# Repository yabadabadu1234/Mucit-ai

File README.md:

# Mucit-ai

## Kur'an Hikmetleri

Kur'an-ı Kerîm'in sûre, nüzûl, tertip ve ayet haritalarını; grafik, sûre dosyaları ve derlenmiş kitabı içeren çalışma.

- **Okunabilir kitap (GitHub Pages):**

- https://yabadabadu1234.github.io/Mucit-ai/
- PDF: [`kuran_hikmetleri/kuran_hikmetleri.pdf`](kuran_hikmetleri/kuran_hikmetleri.pdf)
- Fihrist: [`kuran_hikmetleri/00_FIHRIST.md`](kuran_hikmetleri/00_FIHRIST.md)

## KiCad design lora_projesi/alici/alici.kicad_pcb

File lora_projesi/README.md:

# LoRa remote + receiver – hardware design

- verici/ : transmitter – KiCad files, uretim_dosyalari/ (Gerber, drill, BOM, placement, PDFs), TASARIM_NOTU.md
- alici/ : receiver – KiCad files, uretim_dosyalari/ (Gerber, drill, BOM, placement, PDFs), TASARIM_NOTU.md
- simulasyon/ : ngspice netlists (relay driver, 12 V input protection)
- uretim/ : Python generators (schematic, PCB placement, routing with Freerouting, outputs)
- teklif_taslagi.md, teklif_kisa.txt : offer texts

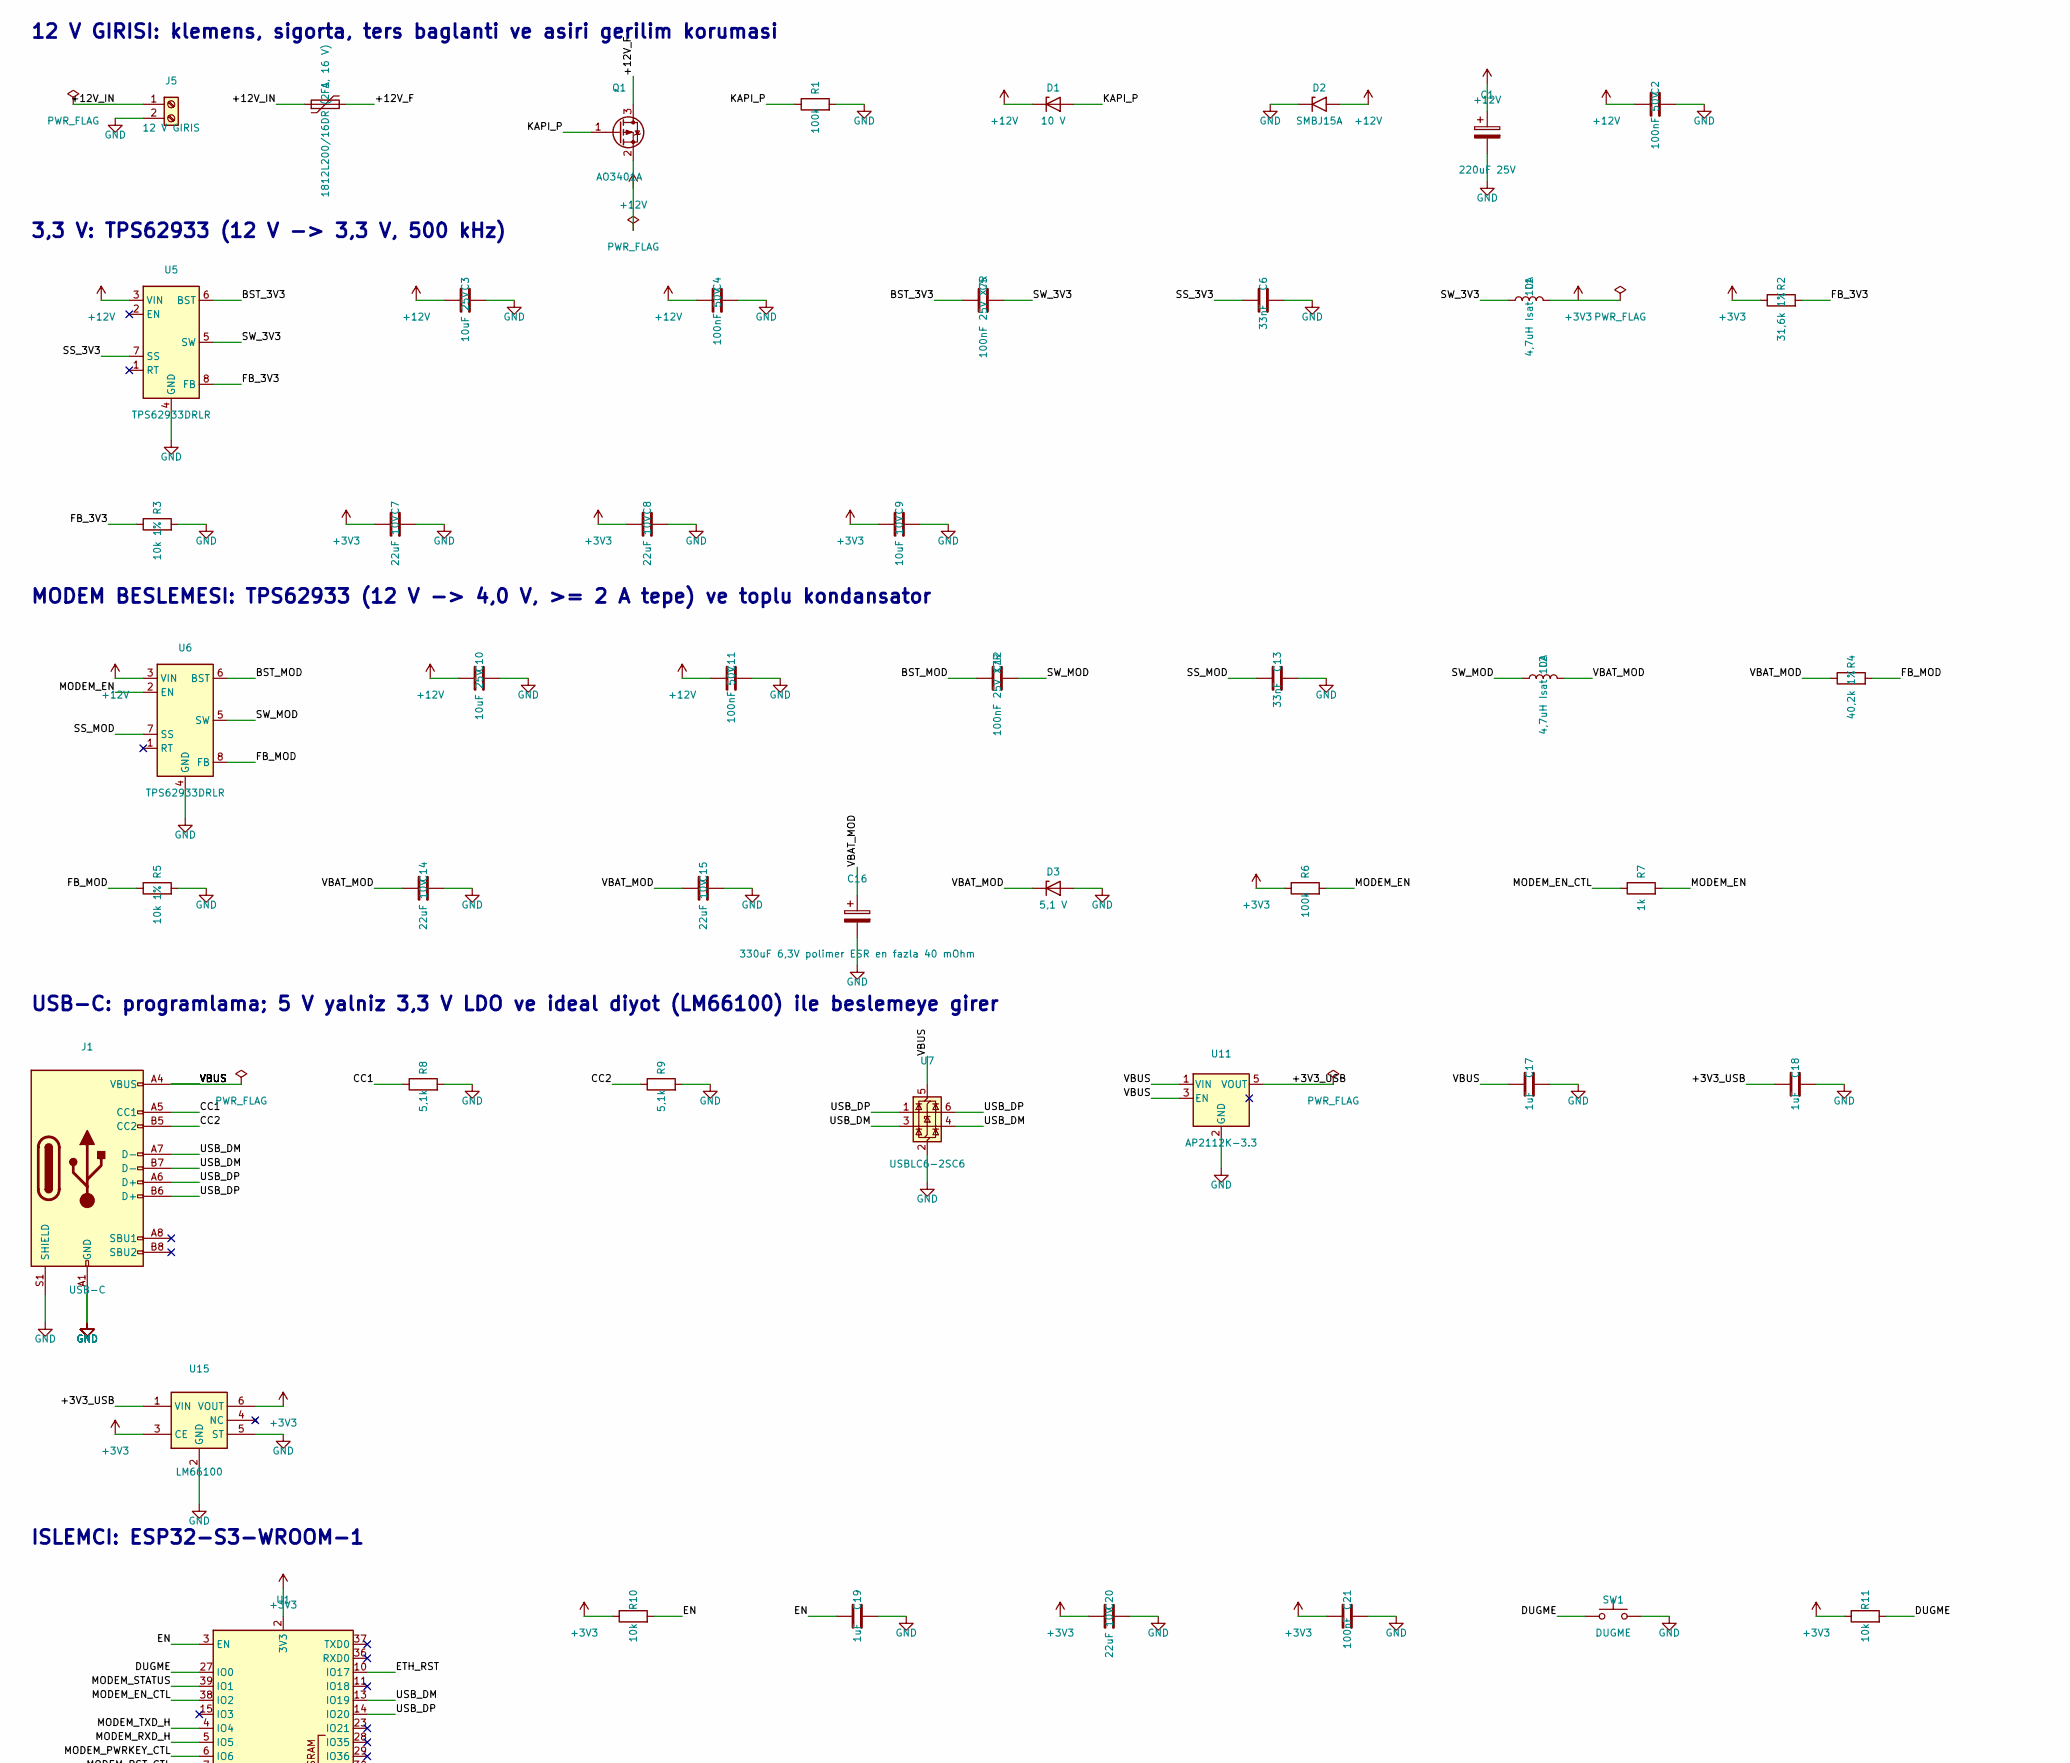
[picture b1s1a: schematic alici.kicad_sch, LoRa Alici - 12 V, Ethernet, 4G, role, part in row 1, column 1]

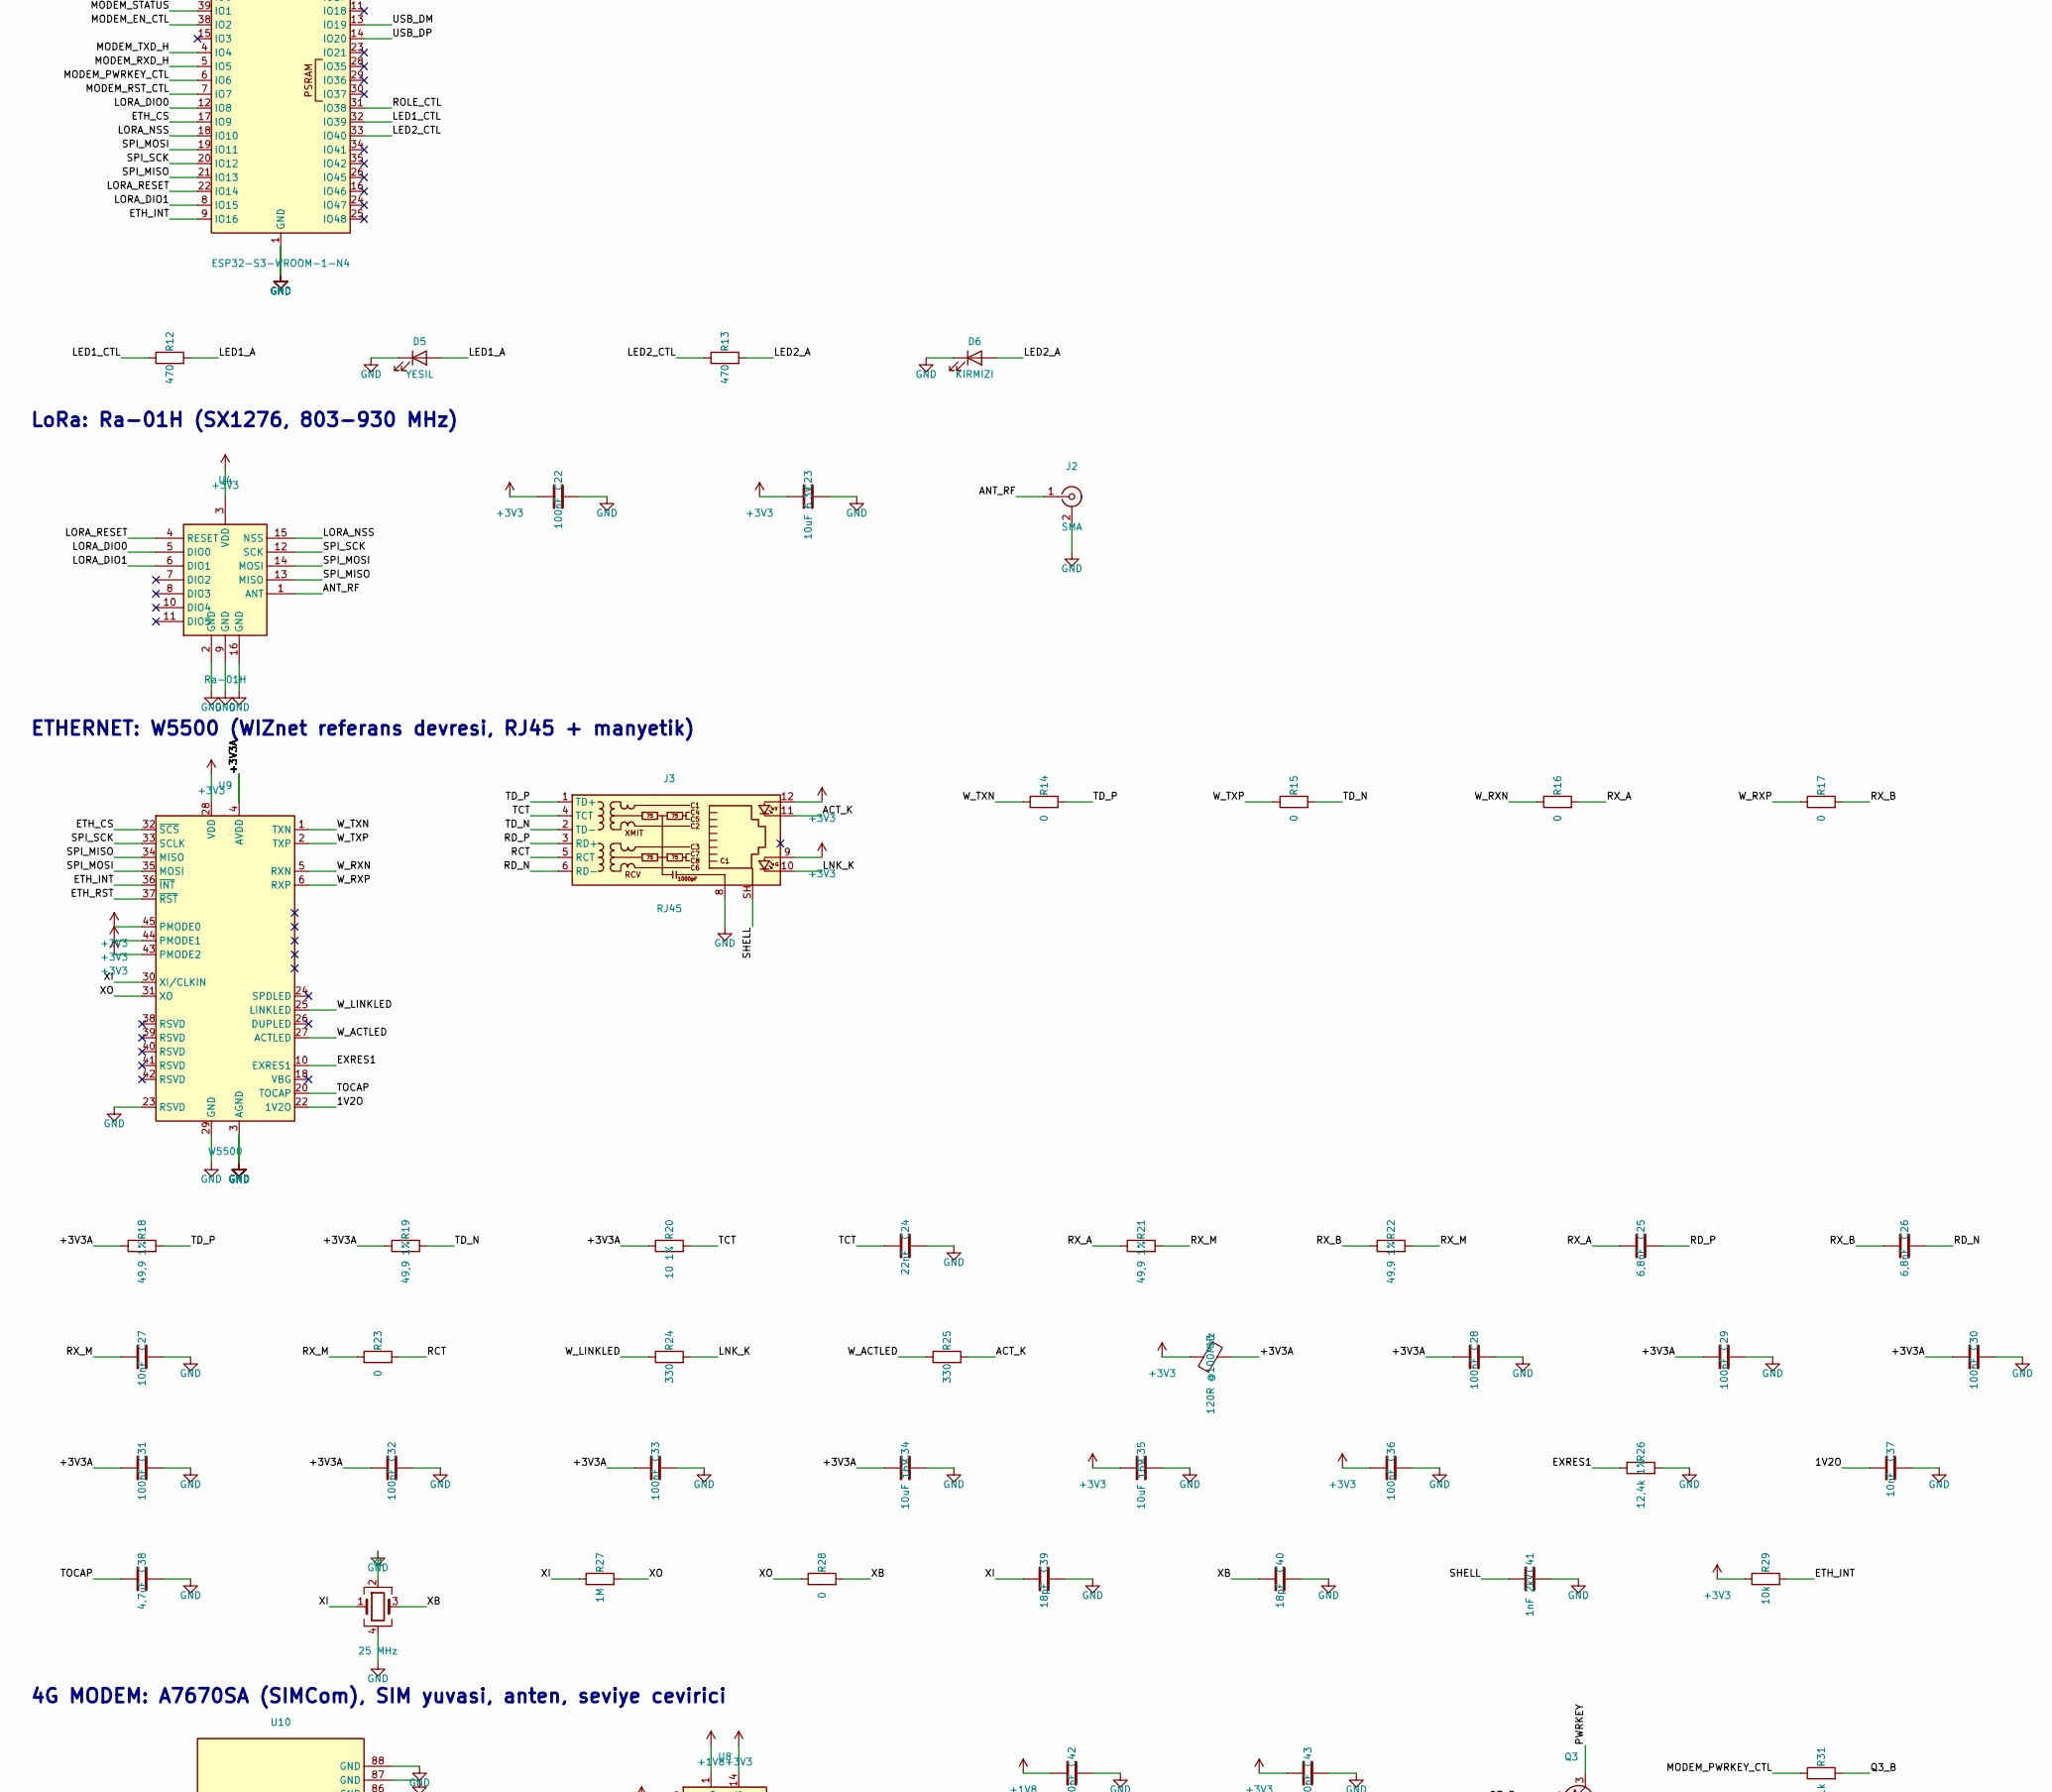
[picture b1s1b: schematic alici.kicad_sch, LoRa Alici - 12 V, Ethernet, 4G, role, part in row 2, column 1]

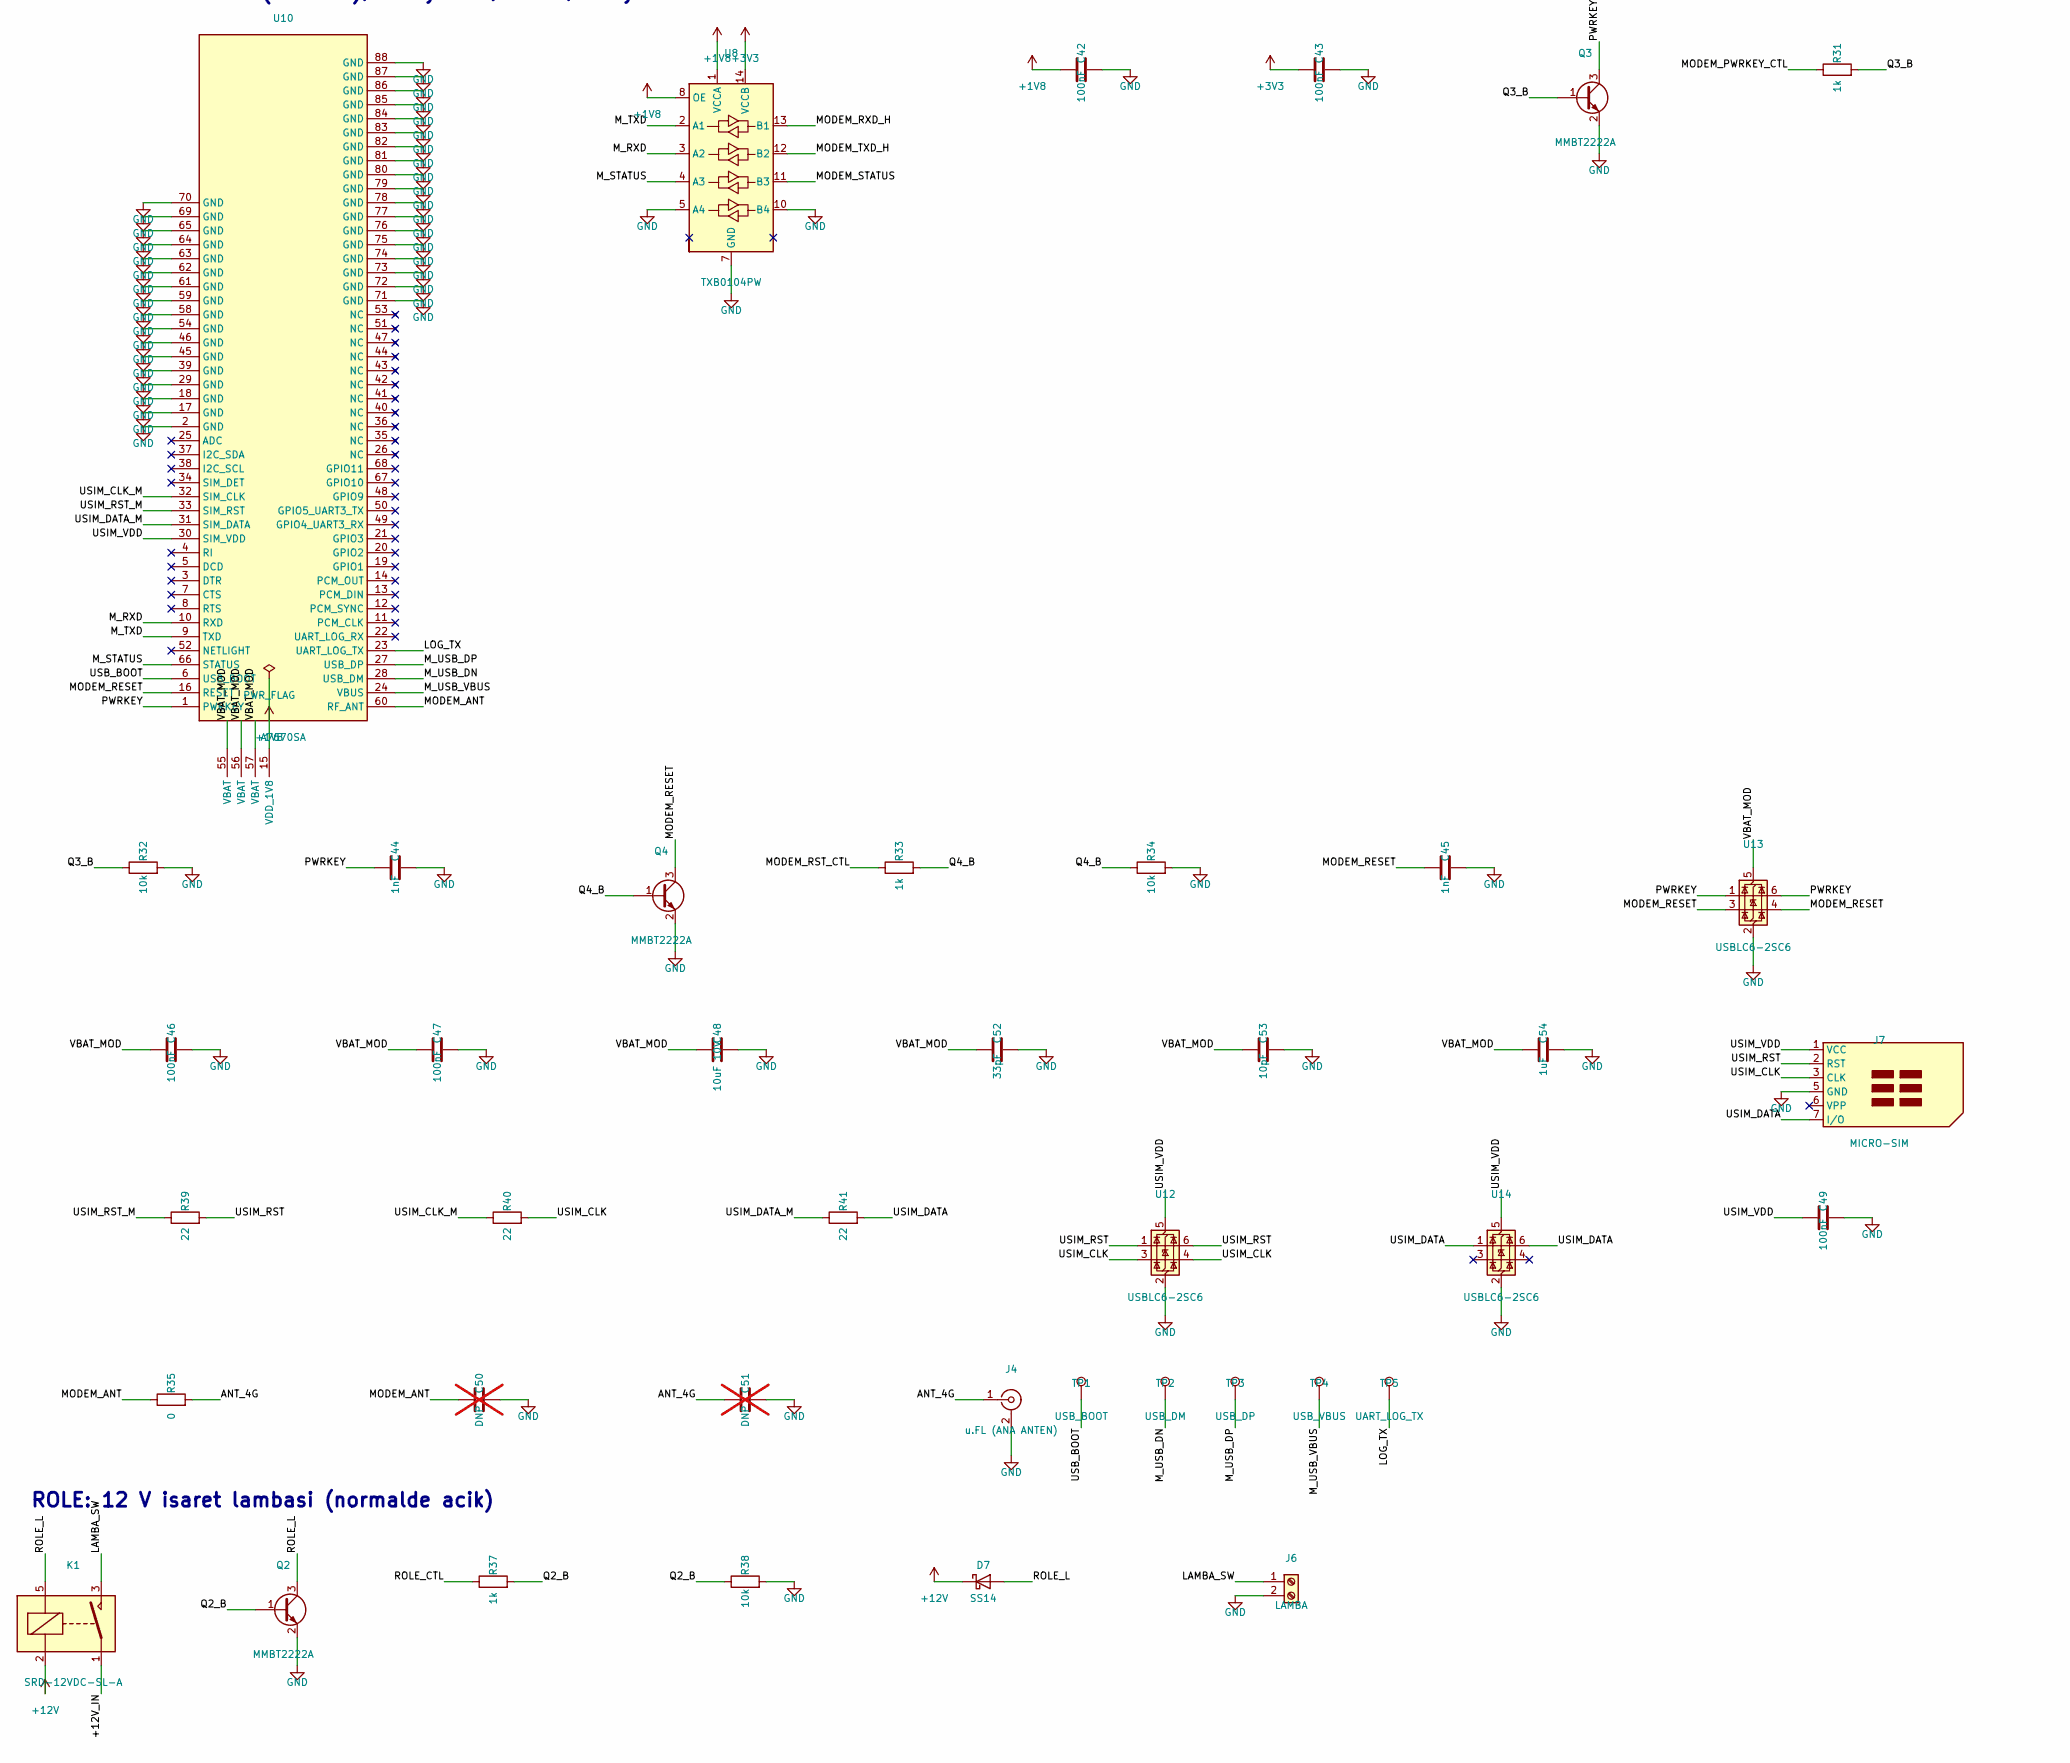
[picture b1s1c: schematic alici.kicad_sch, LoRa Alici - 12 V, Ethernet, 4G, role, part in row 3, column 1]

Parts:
C1: 220uF 25V; CP_Elec_8x10
C2, C4, C11: 100nF 50V; C_0603_1608Metric
C3, C10: 10uF 25V; C_1206_3216Metric
C5, C12: 100nF 25V X7R; C_0603_1608Metric
C6, C13: 33nF; C_0603_1608Metric
C7, C8, C14, C15: 22uF 10V; C_1206_3216Metric
C9, C48: 10uF 10V; C_0603_1608Metric
C16: 330uF 6,3V polimer ESR en fazla 40 mOhm; CP_Elec_6.3x7.7
C17, C18, C19, C54: 1uF; C_0603_1608Metric
C20: 22uF 10V; C_0805_2012Metric
C21, C22, C28, C29, C30, C31, C32, C33, C36, C42, C43, C46, C47, C49: 100nF; C_0603_1608Metric
C23: 10uF 6,3V; C_0603_1608Metric
C24: 22nF; C_0603_1608Metric
C25, C26: 6,8nF; C_0603_1608Metric
C27, C37: 10nF; C_0603_1608Metric
C34, C35: 10uF 16V; C_0603_1608Metric
C38: 4,7uF; C_0603_1608Metric
C39, C40: 18pF; C_0603_1608Metric
C41: 1nF 2kV; C_1206_3216Metric
C44, C45: 1nF; C_0603_1608Metric; MPN A7670 belgesi: PWRKEY ve RESET uzerinde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
C50, C51: DNP; C_0603_1608Metric; not fitted
C52: 33pF; C_0603_1608Metric
C53: 10pF; C_0603_1608Metric
D1: 10 V; D_SOD-123; MPN BZT52C10 (10 V zener)
D2: SMBJ15A; D_SMB; MPN SMBJ15A (tek yonlu 15 V TVS)
D3: 5,1 V; D_SOD-123; MPN BZT52C5V1 (SIMCom onerisi, 500 mW)
D5: YESIL; LED_0603_1608Metric
D6: KIRMIZI; LED_0603_1608Metric
D7: SS14; D_SMA; MPN SS14
F1: 1812L200/16DR (2 A, 16 V); Fuse_1812_4532Metric; MPN Littelfuse 1812L200/16DR (tutma 2 A, 16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
J1: USB-C; USB_C_Receptacle_GCT_USB4105-xx-A_16P_TopMnt_Horizontal; MPN GCT USB4105-GF-A
J2: SMA; SMA_Amphenol_132289_EdgeMount; MPN Amphenol 132289 (kenar SMA)
J3: RJ45; RJ45_Hanrun_HR911105A_Horizontal; MPN HanRun HR911105A
J4: u.FL (ANA ANTEN); U.FL_Hirose_U.FL-R-SMT-1_Vertical; MPN Hirose U.FL-R-SMT-1(10)
J5: 12 V GIRIS; TerminalBlock_Phoenix_MKDS-1,5-2-5.08_1x02_P5.08mm_Horizont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
J6: LAMBA; TerminalBlock_Phoenix_MKDS-1,5-2-5.08_1x02_P5.08mm_Horizont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
J7: MICRO-SIM; microSIM_JAE_SF53S006VCBR2000; MPN JAE SF53S006VCBR2000 (6 uclu micro-SIM)
K1: SRD-12VDC-SL-A; Relay_SPST_SANYOU_SRD_Series_Form_A; MPN Songle SRD-12VDC-SL-A (bobin 400 ohm, k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
L1, L2: 4,7uH Isat 10A; L_Bourns_SRP7028A_7.3x6.6mm; MPN Bourns SRP7028A-4R7M (Isat 10 A, Irms 5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
L3: 120R @100MHz; L_0603_1608Metric; MPN HH-1M1608-121JT (WIZnet referansi)
Q1: AO3401A; SOT-23; MPN AO3401A
Q2, Q3, Q4: MMBT2222A; SOT-23; MPN MMBT2222A
R1, R6: 100k; R_0603_1608Metric
R2: 31,6k 1%; R_0603_1608Metric
R3, R5: 10k 1%; R_0603_1608Metric
R4: 40,2k 1%; R_0603_1608Metric
R7, R31, R33, R37: 1k; R_0603_1608Metric
R8, R9: 5,1k; R_0603_1608Metric
R10, R11, R29, R32, R34, R38: 10k; R_0603_1608Metric
R12, R13: 470; R_0603_1608Metric
R14, R15, R16, R17, R23, R28, R35: 0; R_0603_1608Metric
R18, R19, R21, R22: 49,9 1%; R_0603_1608Metric
R20: 10 1%; R_0603_1608Metric
R24, R25: 330; R_0603_1608Metric
R26: 12,4k 1%; R_0603_1608Metric
R27: 1M; R_0603_1608Metric
R39, R40, R41: 22; R_0603_1608Metric; MPN A7670 belgesi Sekil 19: SIM hatlarina 2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
SW1: DUGME; SW_SPST_TL3342
TP1: USB_BOOT; TestPoint_Pad_1.0x1.0mm
TP2: USB_DM; TestPoint_Pad_1.0x1.0mm
TP3: USB_DP; TestPoint_Pad_1.0x1.0mm
TP4: USB_VBUS; TestPoint_Pad_1.0x1.0mm
TP5: UART_LOG_TX; TestPoint_Pad_1.0x1.0mm
U1: ESP32-S3-WROOM-1-N4; ESP32-S3-WROOM-1; MPN ESP32-S3-WROOM-1-N4
U4: Ra-01H; MPN Ai-Thinker Ra-01H (LCSC C503593)
U5, U6: TPS62933DRLR; SOT-583-8; MPN TPS62933DRLR
U7: USBLC6-2SC6; SOT-23-6; MPN USBLC6-2SC6
U8: TXB0104PW; TSSOP-14_4.4x5mm_P0.65mm; MPN TXB0104PWR
U9: W5500; LQFP-48_7x7mm_P0.5mm; MPN W5500
U10: A7670SA; A7670SA_LGA88; MPN SIMCom A7670SA-LASE (LCSC C47088708; LT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
U11: AP2112K-3.3; SOT-23-5; MPN AP2112K-3.3TRG1
U12: USBLC6-2SC6; SOT-23-6; MPN USBLC6-2SC6 (SIM RST ve CLK ESD; SIMCom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
U13: USBLC6-2SC6; SOT-23-6; MPN USBLC6-2SC6 (PWRKEY ve RESET ESD, hat b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
U14: USBLC6-2SC6; SOT-23-6; MPN USBLC6-2SC6 (SIM DATA ESD; ikinci hat k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
U15: LM66100; SOT-363_SC-70-6; MPN TI LM66100DCKR (ideal diyot, 79-91 mOhm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
Y1: 25 MHz; Crystal_SMD_3225-4Pin_3.2x2.5mm; MPN 25 MHz, 18 pF yuk, +-30 ppm, C0 en fazl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

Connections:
1V2O: C37.1, U9.22 (1V2O)
+1V8: C42.1, U8.1 (VCCA), U8.8 (OE), U10.15 (VDD_1V8)
+3V3: C7.1, C8.1, C9.1, C20.1, C21.1, C22.1, C23.1, C35.1, C36.1, C43.1, J3.9, J3.12, L1.2, L3.1, R2.1, R6.1, R10.1, R11.1, R29.1, U1.2 (3V3), U4.3 (VDD), U8.14 (VCCB), U9.28 (VDD), U9.43 (PMODE2), U9.44 (PMODE1), U9.45 (PMODE0), U15.3 (CE), U15.6 (VOUT)
+3V3A: C28.1, C29.1, C30.1, C31.1, C32.1, C33.1, C34.1, L3.2, R18.1, R19.1, R20.1, U9.4 (AVDD), U9.8 (AVDD), U9.11 (AVDD), U9.15 (AVDD), U9.17 (AVDD), U9.21 (AVDD)
+3V3_USB: C18.1, U11.5 (VOUT), U15.1 (VIN)
+12V: C1.1, C2.1, C3.1, C4.1, C10.1, C11.1, D1.1 (K), D2.2 (A2), D7.1 (K), K1.2, Q1.2 (S), U5.3 (VIN), U6.3 (VIN)
+12V_F: F1.2, Q1.3 (D)
+12V_IN: F1.1, J5.1, K1.1
ACT_K: J3.11, R25.2
ANT_4G: C51.1, J4.1 (In), R35.2
ANT_RF: J2.1 (In), U4.1 (ANT)
BST_3V3: C5.1, U5.6 (BST)
BST_MOD: C12.1, U6.6 (BST)
CC1: J1.A5 (CC1), R8.1
CC2: J1.B5 (CC2), R9.1
DUGME: R11.2, SW1.1, U1.27 (IO0)
EN: C19.1, R10.2, U1.3 (EN)
ETH_CS: U1.17 (IO9), U9.32 (~SCS)
ETH_INT: R29.2, U1.9 (IO16), U9.36 (~INT)
ETH_RST: U1.10 (IO17), U9.37 (~RST)
EXRES1: R26.1, U9.10 (EXRES1)
FB_3V3: R2.2, R3.1, U5.8 (FB)
FB_MOD: R4.2, R5.1, U6.8 (FB)
GND: C1.2, C2.2, C3.2, C4.2, C6.2, C7.2, C8.2, C9.2, C10.2, C11.2, C13.2, C14.2, C15.2, C16.2, C17.2, C18.2, C19.2, C20.2, C21.2, C22.2, C23.2, C24.2, C27.2, C28.2, C29.2, C30.2, C31.2, C32.2, C33.2, C34.2, C35.2, C36.2, C37.2, C38.2, C39.2, C40.2, C41.2, C42.2, C43.2, C44.2, C45.2, C46.2, C47.2, C48.2, C49.2, C50.2, C51.2, C52.2, C53.2, C54.2, D2.1 (A1), D3.2 (A), D5.1 (K), D6.1 (K), J1.A1 (GND), J1.A12 (GND), J1.B1 (GND), J1.B12 (GND), J1.S1 (SHIELD), J2.2 (Ext), J3.8, J4.2 (Ext), J5.2, J6.2, J7.5 (GND), Q2.2 (E), Q3.2 (E), Q4.2 (E), R1.2, R3.2, R5.2, R8.2, R9.2, R26.2, R32.2, R34.2, R38.2, SW1.2, U1.1 (GND), U1.40 (GND), U1.41 (GND), U4.2 (GND), U4.9 (GND), U4.16 (GND), U5.4 (GND), U6.4 (GND), U7.2 (GND), U8.5 (A4), U8.7 (GND), U8.10 (B4), U9.3 (AGND), U9.9 (AGND), U9.14 (AGND), U9.16 (AGND), U9.19 (AGND), U9.23 (RSVD), U9.29 (GND), U9.48 (AGND), U10.2 (GND), U10.17 (GND), U10.18 (GND), U10.29 (GND), U10.39 (GND), U10.45 (GND), U10.46 (GND), U10.54 (GND), U10.58 (GND), U10.59 (GND), U10.61 (GND), U10.62 (GND), U10.63 (GND), U10.64 (GND), U10.65 (GND), U10.69 (GND), U10.70 (GND), U10.71 (GND), U10.72 (GND), U10.73 (GND), U10.74 (GND), U10.75 (GND), U10.76 (GND), U10.77 (GND), U10.78 (GND), U10.79 (GND), U10.80 (GND), U10.81 (GND), U10.82 (GND), U10.83 (GND), U10.84 (GND), U10.85 (GND), U10.86 (GND), U10.87 (GND), U10.88 (GND), U11.2 (GND), U12.2 (GND), U13.2 (GND), U14.2 (GND), U15.2 (GND), U15.5 (ST), Y1.2, Y1.4
KAPI_P: D1.2 (A), Q1.1 (G), R1.1
LAMBA_SW: J6.1, K1.3
LED1_A: D5.2 (A), R12.2
LED1_CTL: R12.1, U1.32 (IO39)
LED2_A: D6.2 (A), R13.2
LED2_CTL: R13.1, U1.33 (IO40)
LNK_K: J3.10, R24.2
LOG_TX: TP5.1, U10.23 (UART_LOG_TX)
LORA_DIO0: U1.12 (IO8), U4.5 (DIO0)
LORA_DIO1: U1.8 (IO15), U4.6 (DIO1)
LORA_NSS: U1.18 (IO10), U4.15 (NSS)
LORA_RESET: U1.22 (IO14), U4.4 (RESET)
MODEM_ANT: C50.1, R35.1, U10.60 (RF_ANT)
MODEM_EN: R6.2, R7.2, U6.2 (EN)
MODEM_EN_CTL: R7.1, U1.38 (IO2)
MODEM_PWRKEY_CTL: R31.1, U1.6 (IO6)
MODEM_RESET: C45.1, Q4.3 (C), U10.16 (RESET), U13.3 (I/O2), U13.4 (I/O2)
MODEM_RST_CTL: R33.1, U1.7 (IO7)
MODEM_RXD_H: U1.5 (IO5), U8.13 (B1)
MODEM_STATUS: U1.39 (IO1), U8.11 (B3)
MODEM_TXD_H: U1.4 (IO4), U8.12 (B2)
M_RXD: U8.3 (A2), U10.10 (RXD)
M_STATUS: U8.4 (A3), U10.66 (STATUS)
M_TXD: U8.2 (A1), U10.9 (TXD)
M_USB_DN: TP2.1, U10.28 (USB_DM)
M_USB_DP: TP3.1, U10.27 (USB_DP)
M_USB_VBUS: TP4.1, U10.24 (VBUS)
PWRKEY: C44.1, Q3.3 (C), U10.1 (PWRKEY), U13.1 (I/O1), U13.6 (I/O1)
Q2_B: Q2.1 (B), R37.2, R38.1
Q3_B: Q3.1 (B), R31.2, R32.1
Q4_B: Q4.1 (B), R33.2, R34.1
RCT: J3.5 (RCT), R23.2
RD_N: C26.2, J3.6 (RD-)
RD_P: C25.2, J3.3 (RD+)
ROLE_CTL: R37.1, U1.31 (IO38)
ROLE_L: D7.2 (A), K1.5, Q2.3 (C)
RX_A: C25.1, R16.2, R21.1
RX_B: C26.1, R17.2, R22.1
RX_M: C27.1, R21.2, R22.2, R23.1
SHELL: C41.1, J3.SH
SPI_MISO: U1.21 (IO13), U4.13 (MISO), U9.34 (MISO)
SPI_MOSI: U1.19 (IO11), U4.14 (MOSI), U9.35 (MOSI)
SPI_SCK: U1.20 (IO12), U4.12 (SCK), U9.33 (SCLK)
SS_3V3: C6.1, U5.7 (SS)
SS_MOD: C13.1, U6.7 (SS)
SW_3V3: C5.2, L1.1, U5.5 (SW)
SW_MOD: C12.2, L2.1, U6.5 (SW)
TCT: C24.1, J3.4 (TCT), R20.2
TD_N: J3.2 (TD-), R15.2, R19.2
TD_P: J3.1 (TD+), R14.2, R18.2
TOCAP: C38.1, U9.20 (TOCAP)
USB_BOOT: TP1.1, U10.6 (USB_BOOT)
USB_DM: J1.A7 (D-), J1.B7 (D-), U1.13 (IO19), U7.3 (I/O2), U7.4 (I/O2)
USB_DP: J1.A6 (D+), J1.B6 (D+), U1.14 (IO20), U7.1 (I/O1), U7.6 (I/O1)
USIM_CLK: J7.3 (CLK), R40.2, U12.3 (I/O2), U12.4 (I/O2)
USIM_CLK_M: R40.1, U10.32 (SIM_CLK)
USIM_DATA: J7.7 (I/O), R41.2, U14.1 (I/O1), U14.6 (I/O1)
USIM_DATA_M: R41.1, U10.31 (SIM_DATA)
USIM_RST: J7.2 (RST), R39.2, U12.1 (I/O1), U12.6 (I/O1)
USIM_RST_M: R39.1, U10.33 (SIM_RST)
USIM_VDD: C49.1, J7.1 (VCC), U10.30 (SIM_VDD), U12.5 (VBUS), U14.5 (VBUS)
VBAT_MOD: C14.1, C15.1, C16.1, C46.1, C47.1, C48.1, C52.1, C53.1, C54.1, D3.1 (K), L2.2, R4.1, U10.55 (VBAT), U10.56 (VBAT), U10.57 (VBAT), U13.5 (VBUS)
VBUS: C17.1, J1.A4 (VBUS), J1.A9 (VBUS), J1.B4 (VBUS), J1.B9 (VBUS), U7.5 (VBUS), U11.1 (VIN), U11.3 (EN)
W_ACTLED: R25.1, U9.27 (ACTLED)
W_LINKLED: R24.1, U9.25 (LINKLED)
W_RXN: R16.1, U9.5 (RXN)
W_RXP: R17.1, U9.6 (RXP)
W_TXN: R14.1, U9.1 (TXN)
W_TXP: R15.1, U9.2 (TXP)
XB: C40.1, R28.2, Y1.3
XI: C39.1, R27.1, U9.30 (XI/CLKIN), Y1.1
XO: R27.2, R28.1, U9.31 (XO)

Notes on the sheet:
12 V GIRISI: klemens, sigorta, ters baglanti ve asiri gerilim korumasi
3,3 V: TPS62933 (12 V -> 3,3 V, 500 kHz)
MODEM BESLEMESI: TPS62933 (12 V -> 4,0 V, >= 2 A tepe) ve toplu kondansator
USB-C: programlama; 5 V yalniz 3,3 V LDO ve ideal diyot (LM66100) ile beslemeye girer
ISLEMCI: ESP32-S3-WROOM-1
LoRa: Ra-01H (SX1276, 803-930 MHz)
ETHERNET: W5500 (WIZnet referans devresi, RJ45 + manyetik)
4G MODEM: A7670SA (SIMCom), SIM yuvasi, anten, seviye cevirici
ROLE: 12 V isaret lambasi (normalde acik)

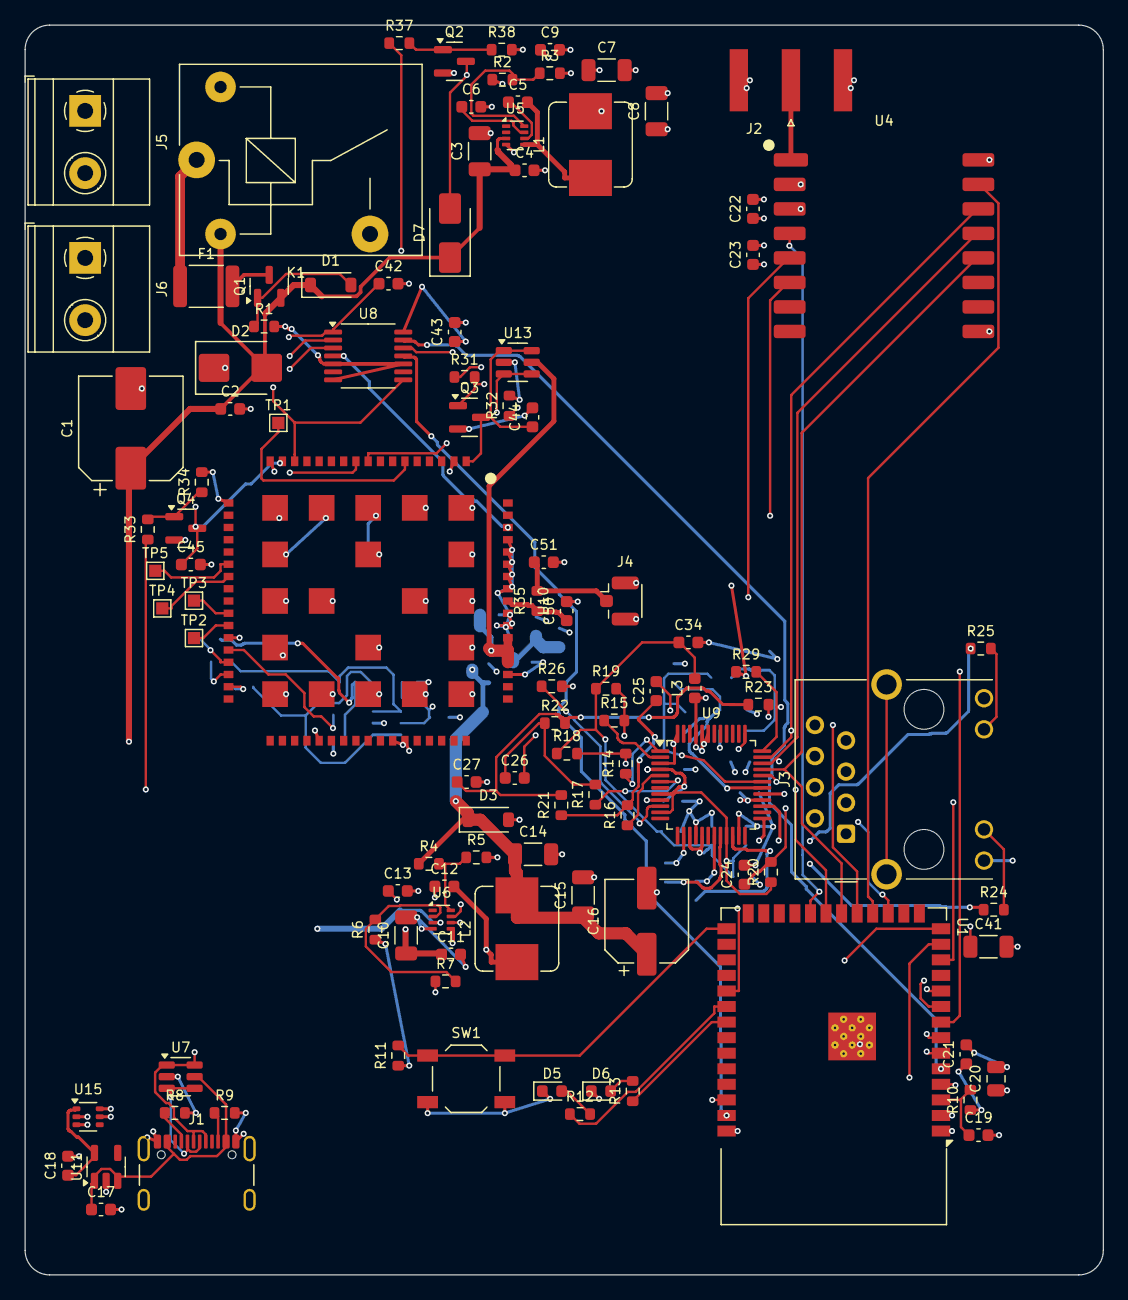
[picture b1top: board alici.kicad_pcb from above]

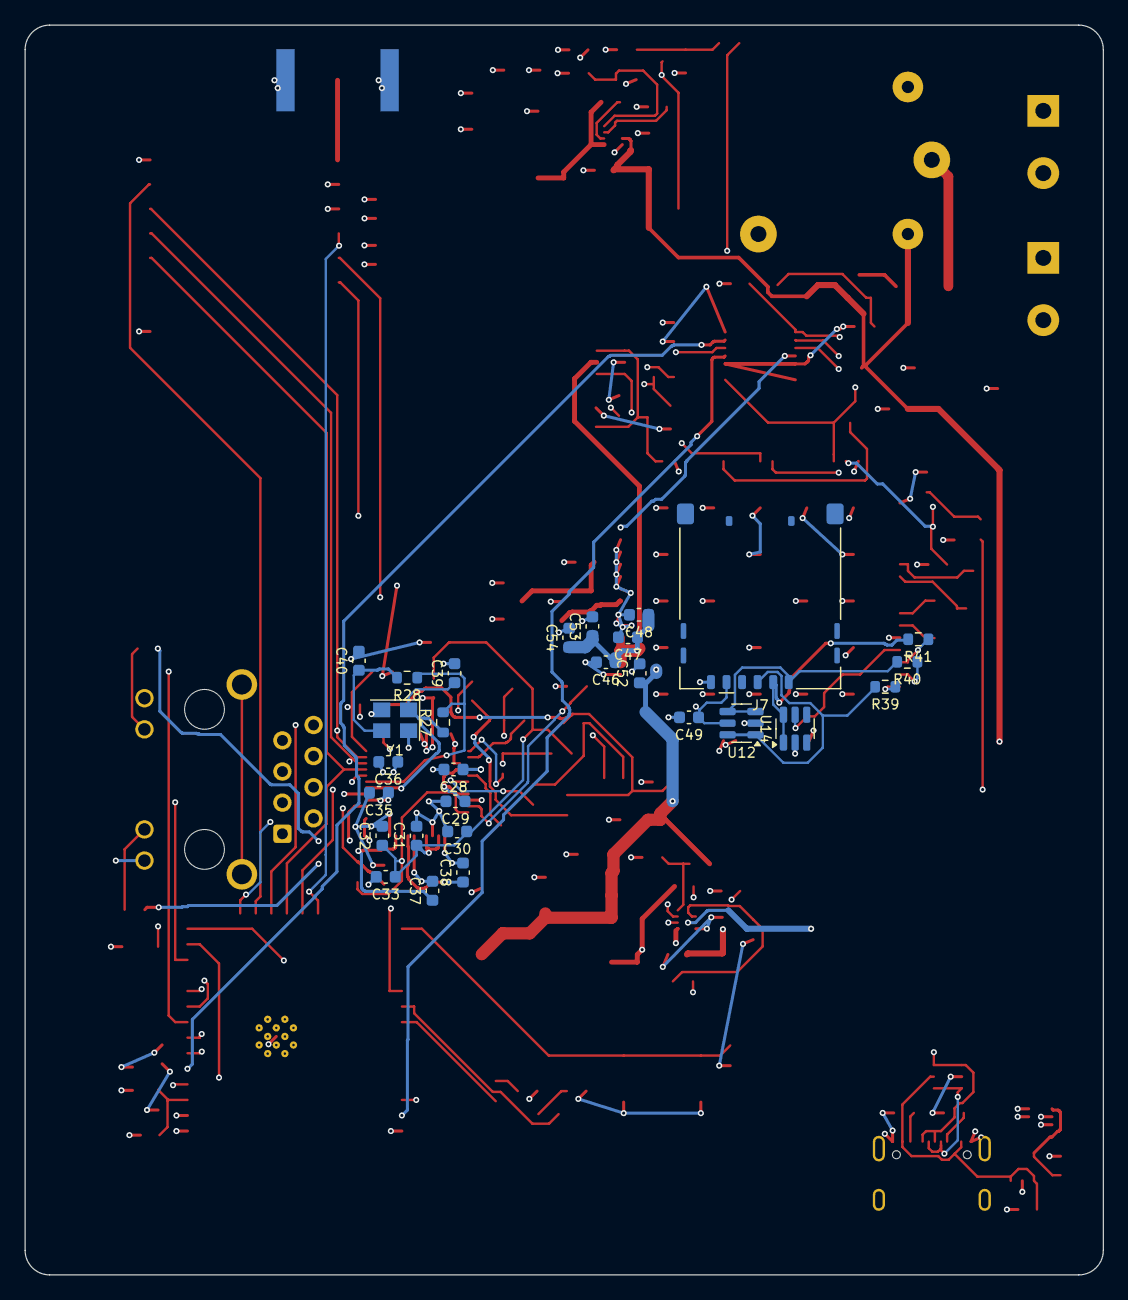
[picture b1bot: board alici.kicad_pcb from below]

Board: 4 copper layers, 88.0 x 102.0 mm, 135 parts (28 on the bottom side), 96 nets.
